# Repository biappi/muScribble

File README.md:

# µScribble

An hardware USB [Scribble Strip](https://www.sweetwater.com/insync/scribble-strip/)
 that supports the Mackie Control Protocol.

## Introduction

µScribble is an USB Midi gadget designed to be a companion to inexpensive faderboxes
without displays. It should be compatible with any DAW that supports control surfaces.
I've personally used it with [Apple Logic Pro](https://www.apple.com/logic-pro/) and
[Ableton Live](https://www.ableton.com/en/live/).

The hardware itself is very simple an d based around an
[STM32F4](https://www.st.com/en/microcontrollers-microprocessors/stm32f4-series.html)
evaluation board, sometimes known as "blackpill", while the displays are the SPI variant
of the ubiquitous [SSD1306 OLED screens](https://cdn-shop.adafruit.com/datasheets/SSD1306.pdf).

The software is implemented using the [unicore-mx](https://github.com/insane-adding-machines/unicore-mx)
fork of [libopencm3](https://github.com/libopencm3/libopencm3) as it has a slighlty
better support for the stm32 target platform. It should be relatively easy to port
the application code to any microcontroller of choice.

## Hardware design files

The hardware is designed using the [KiCad EDA](https://kicad.org)

* [KiCad project directory](hardware/kicad)
* [Schematic diagram PDF](hardware/images/schema.pdf)

* [Gerber fabrication files directory](hardware/gerbers)

## Software

The firmware depends on the `arm-none-eabi-gcc` toolchain, and to compile it
it's sufficient to invoke

```
make
```

As a convenience, if you have the [STLink](https://github.com/stlink-org/stlink/)
tools installed, you can flash the firmware to the device using the `st-flash` command
with

```
make flash
```

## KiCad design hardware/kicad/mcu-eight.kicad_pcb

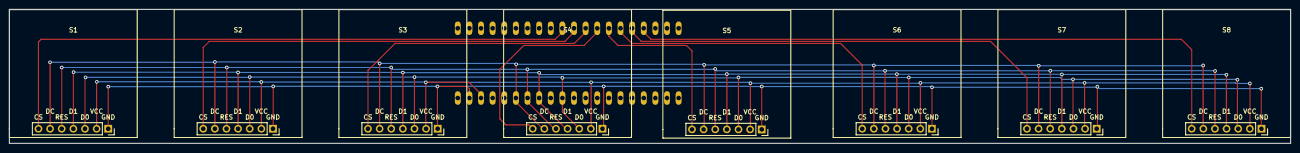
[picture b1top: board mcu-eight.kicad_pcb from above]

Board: 2 copper layers, 280.0 x 29.3 mm, 9 parts (1 on the bottom side), 14 nets.

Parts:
S1: Screen 1; display-spi
S2: Screen 2; display-spi
S3: Screen 3; display-spi
S4: Screen 4; display-spi
S5: Screen 5; display-spi
S6: Screen 6; display-spi
S7: Screen 7; display-spi
S8: Screen 8; display-spi
U1: MCU; YAAJ_BohPill

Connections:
3v3: S1.2, S2.2, S3.2, S4.2, S5.2, S6.2, S7.2, S8.2, U1.38
CS1: S1.7, U1.10
CS2: S2.7, U1.11
CS3: S3.7, U1.12
CS4: S4.7, U1.13
CS5: S5.7, U1.14
CS6: S6.7, U1.15
CS7: S7.7, U1.16
CS8: S8.7, U1.17
D_DC#: S1.6, S2.6, S3.6, S4.6, S5.6, S6.6, S7.6, S8.6, U1.35
D_RES: S1.5, S2.5, S3.5, S4.5, S5.5, S6.5, S7.5, S8.5, U1.34
GND: S1.1, S2.1, S3.1, S4.1, S5.1, S6.1, S7.1, S8.1, U1.39
SPI_CLK: S1.3, S2.3, S3.3, S4.3, S5.3, S6.3, S7.3, S8.3, U1.31
SPI_MOSI: S1.4, S2.4, S3.4, S4.4, S5.4, S6.4, S7.4, S8.4, U1.33

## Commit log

2019-10-17 example
2019-10-24 adding the usb midi interface code
2019-10-28 compile unicore before any app target
2019-10-28 splitting cdcacm and usb-midi out of main
2019-10-28 adding an spi-screen test
2019-10-28 adding a gitignore
2019-10-30 fixing display and font orientation
2019-10-30 adding vim swapfiles to gitignore
2019-10-30 re-imported the unicore-mx usbmidi example, deleted the usb cdcacm class
2019-11-01 test midi input
2019-11-01 splitted out files from main
2019-11-01 correctly unframing sysex messages and parsing the logic control strip
2019-11-04 parsing logic control strip
2020-04-07 adding the pcb kicad project file
2020-04-21 updated pin configuration for the board, and implement display CS selection
2020-04-21 add a phony target to flash the device
2020-04-21 display the MCU strips
2020-04-22 add funny glyphs
2020-04-22 adding functions to print double size fonts
2020-04-30 adding a tentative 3d printer holder
2020-05-04 initial implementation of a systick
2020-05-04 better link to libc
2020-05-04 change the first display to avoid a stale character during updates
2020-05-04 displaying system time as debug
2020-05-04 redraw screens less often
2020-05-05 respond to vu-meter data
2020-05-05 different style of main loop, still unsatisfactory
2020-05-05 fancier vumeter
2020-05-05 add a way to invert the display
2020-05-05 tweak the main loop code
2020-05-05 up the cpu clock
2020-08-28 media files for readme
2021-11-09 Update README.md
    https://forum.kicad.info/t/warning-avoid-all-links-to-kicad-pcb-org-use-kicad-org/31521
